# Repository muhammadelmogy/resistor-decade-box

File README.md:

# resistor-decade-box
0.5W resistor 7 decade box

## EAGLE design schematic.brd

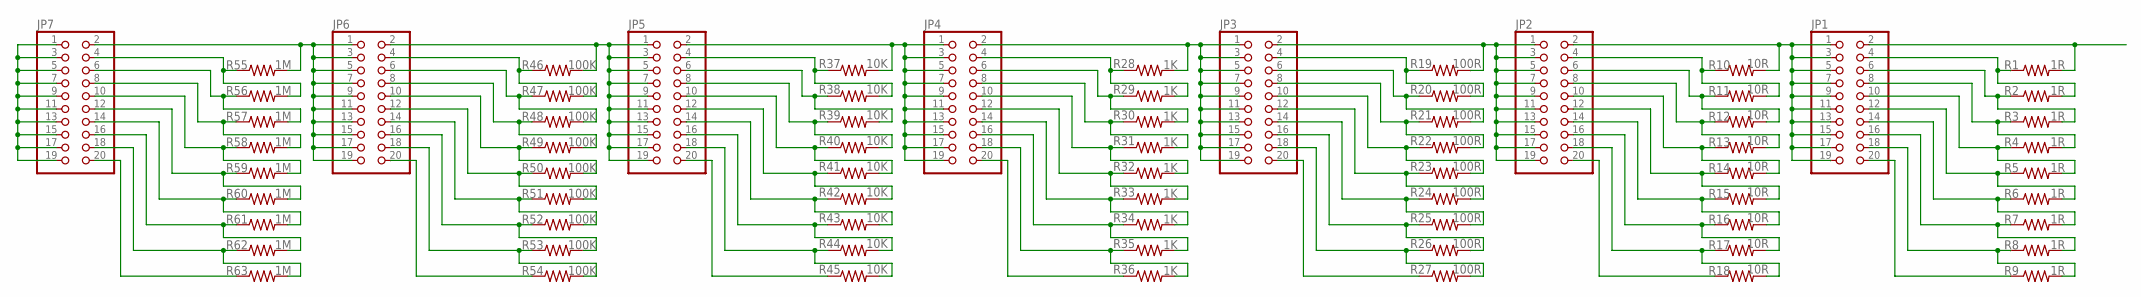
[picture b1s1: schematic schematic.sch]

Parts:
JP1, JP2, JP3, JP4, JP5, JP6, JP7: PINHD-2X10_2.54-SMD; 2X10SMD
R1, R2, R3, R4, R5, R6, R7, R8, R9: 1R; 1206
R10, R11, R12, R13, R14, R15, R16, R17, R18: 10R; R2512
R19, R20, R21, R22, R23, R24, R25, R26, R27: 100R; R2512
R28, R29, R30, R31, R32, R33, R34, R35, R36: 1K; R2512
R37, R38, R39, R40, R41, R42, R43, R44, R45: 10K; R2512
R46, R47, R48, R49, R50, R51, R52, R53, R54: 100K; R2512
R55, R56, R57, R58, R59, R60, R61, R62, R63: 1M; R2512

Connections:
unnamed: JP1.1, JP1.3, JP1.5, JP1.7, JP1.9, JP1.11, JP1.13, JP1.15, JP1.17, JP1.19, JP2.2, R10.2
unnamed: JP1.2, R1.2
unnamed: JP1.6, R2.1, R3.2
unnamed: JP1.4, R1.1, R2.2
unnamed: JP1.8, R3.1, R4.2
unnamed: JP1.10, R4.1, R5.2
unnamed: JP1.12, R5.1, R6.2
unnamed: JP1.14, R6.1, R7.2
unnamed: JP1.16, R7.1, R8.2
unnamed: JP1.18, R8.1, R9.2
unnamed: JP1.20, R9.1
unnamed: JP2.1, JP2.3, JP2.5, JP2.7, JP2.9, JP2.11, JP2.13, JP2.15, JP2.17, JP2.19, JP3.2, R19.2
unnamed: JP4.1, JP4.3, JP4.5, JP4.7, JP4.9, JP4.11, JP4.13, JP4.15, JP4.17, JP4.19, JP5.2, R37.2
unnamed: JP2.4, R10.1, R11.2
unnamed: JP2.6, R11.1, R12.2
unnamed: JP2.8, R12.1, R13.2
unnamed: JP2.10, R13.1, R14.2
unnamed: JP2.12, R14.1, R15.2
unnamed: JP2.14, R15.1, R16.2
unnamed: JP2.16, R16.1, R17.2
unnamed: JP2.18, R17.1, R18.2
unnamed: JP2.20, R18.1
unnamed: JP3.1, JP3.3, JP3.5, JP3.7, JP3.9, JP3.11, JP3.13, JP3.15, JP3.17, JP3.19, JP4.2, R28.2
unnamed: JP6.1, JP6.3, JP6.5, JP6.7, JP6.9, JP6.11, JP6.13, JP6.15, JP6.17, JP6.19, JP7.2, R55.2
unnamed: JP3.4, R19.1, R20.2
unnamed: JP3.6, R20.1, R21.2
unnamed: JP3.8, R21.1, R22.2
unnamed: JP3.10, R22.1, R23.2
unnamed: JP3.12, R23.1, R24.2
unnamed: JP3.14, R24.1, R25.2
unnamed: JP3.16, R25.1, R26.2
unnamed: JP3.18, R26.1, R27.2
unnamed: JP3.20, R27.1
unnamed: JP4.4, R28.1, R29.2
unnamed: JP4.6, R29.1, R30.2
unnamed: JP4.8, R30.1, R31.2
unnamed: JP4.10, R31.1, R32.2
unnamed: JP4.12, R32.1, R33.2
unnamed: JP4.14, R33.1, R34.2
unnamed: JP4.16, R34.1, R35.2
unnamed: JP4.18, R35.1, R36.2
unnamed: JP4.20, R36.1
unnamed: JP5.1, JP5.3, JP5.5, JP5.7, JP5.9, JP5.11, JP5.13, JP5.15, JP5.17, JP5.19, JP6.2, R46.2
unnamed: JP5.4, R37.1, R38.2
unnamed: JP5.6, R38.1, R39.2
unnamed: JP5.8, R39.1, R40.2
unnamed: JP5.10, R40.1, R41.2
unnamed: JP5.12, R41.1, R42.2
unnamed: JP5.14, R42.1, R43.2
unnamed: JP5.16, R43.1, R44.2
unnamed: JP5.18, R44.1, R45.2
unnamed: JP5.20, R45.1
unnamed: JP7.1, JP7.3, JP7.5, JP7.7, JP7.9, JP7.11, JP7.13, JP7.15, JP7.17, JP7.19
unnamed: JP6.4, R46.1, R47.2
unnamed: JP6.6, R47.1, R48.2
unnamed: JP6.8, R48.1, R49.2
unnamed: JP6.10, R49.1, R50.2
unnamed: JP6.12, R50.1, R51.2
unnamed: JP6.14, R51.1, R52.2
unnamed: JP6.16, R52.1, R53.2
unnamed: JP6.18, R53.1, R54.2
unnamed: JP6.20, R54.1
unnamed: JP7.4, R55.1, R56.2
unnamed: JP7.6, R56.1, R57.2
unnamed: JP7.8, R57.1, R58.2
unnamed: JP7.10, R58.1, R59.2
unnamed: JP7.12, R59.1, R60.2
unnamed: JP7.14, R60.1, R61.2
unnamed: JP7.16, R61.1, R62.2
unnamed: JP7.18, R62.1, R63.2
unnamed: JP7.20, R63.1

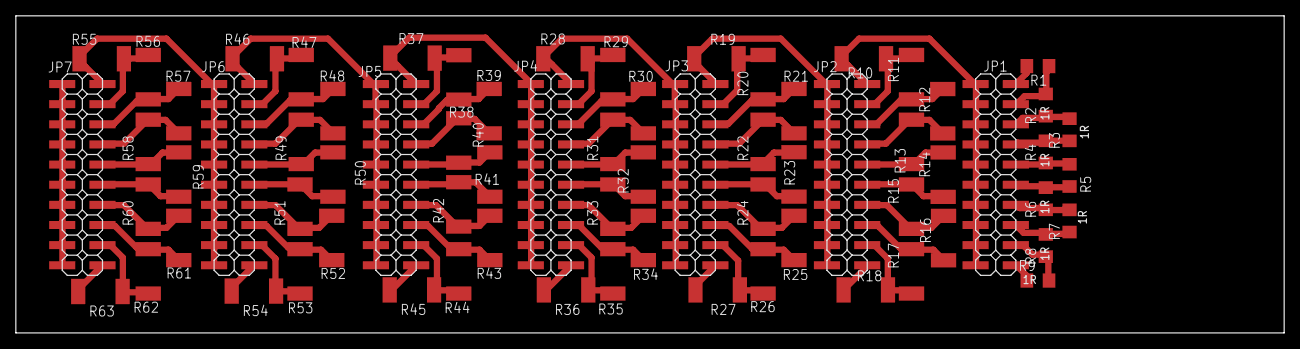
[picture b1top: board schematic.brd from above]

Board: 2 copper layers, 160.0 x 40.0 mm, 70 parts (0 on the bottom side), 71 nets.

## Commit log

2019-03-12 working on the PCB layout

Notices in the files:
parts and their libraries:
SparkFun-Passives: Licensing: Creative Commons ShareAlike 4.0 International - https://creativecommons.org/licenses/by-sa/4.0
